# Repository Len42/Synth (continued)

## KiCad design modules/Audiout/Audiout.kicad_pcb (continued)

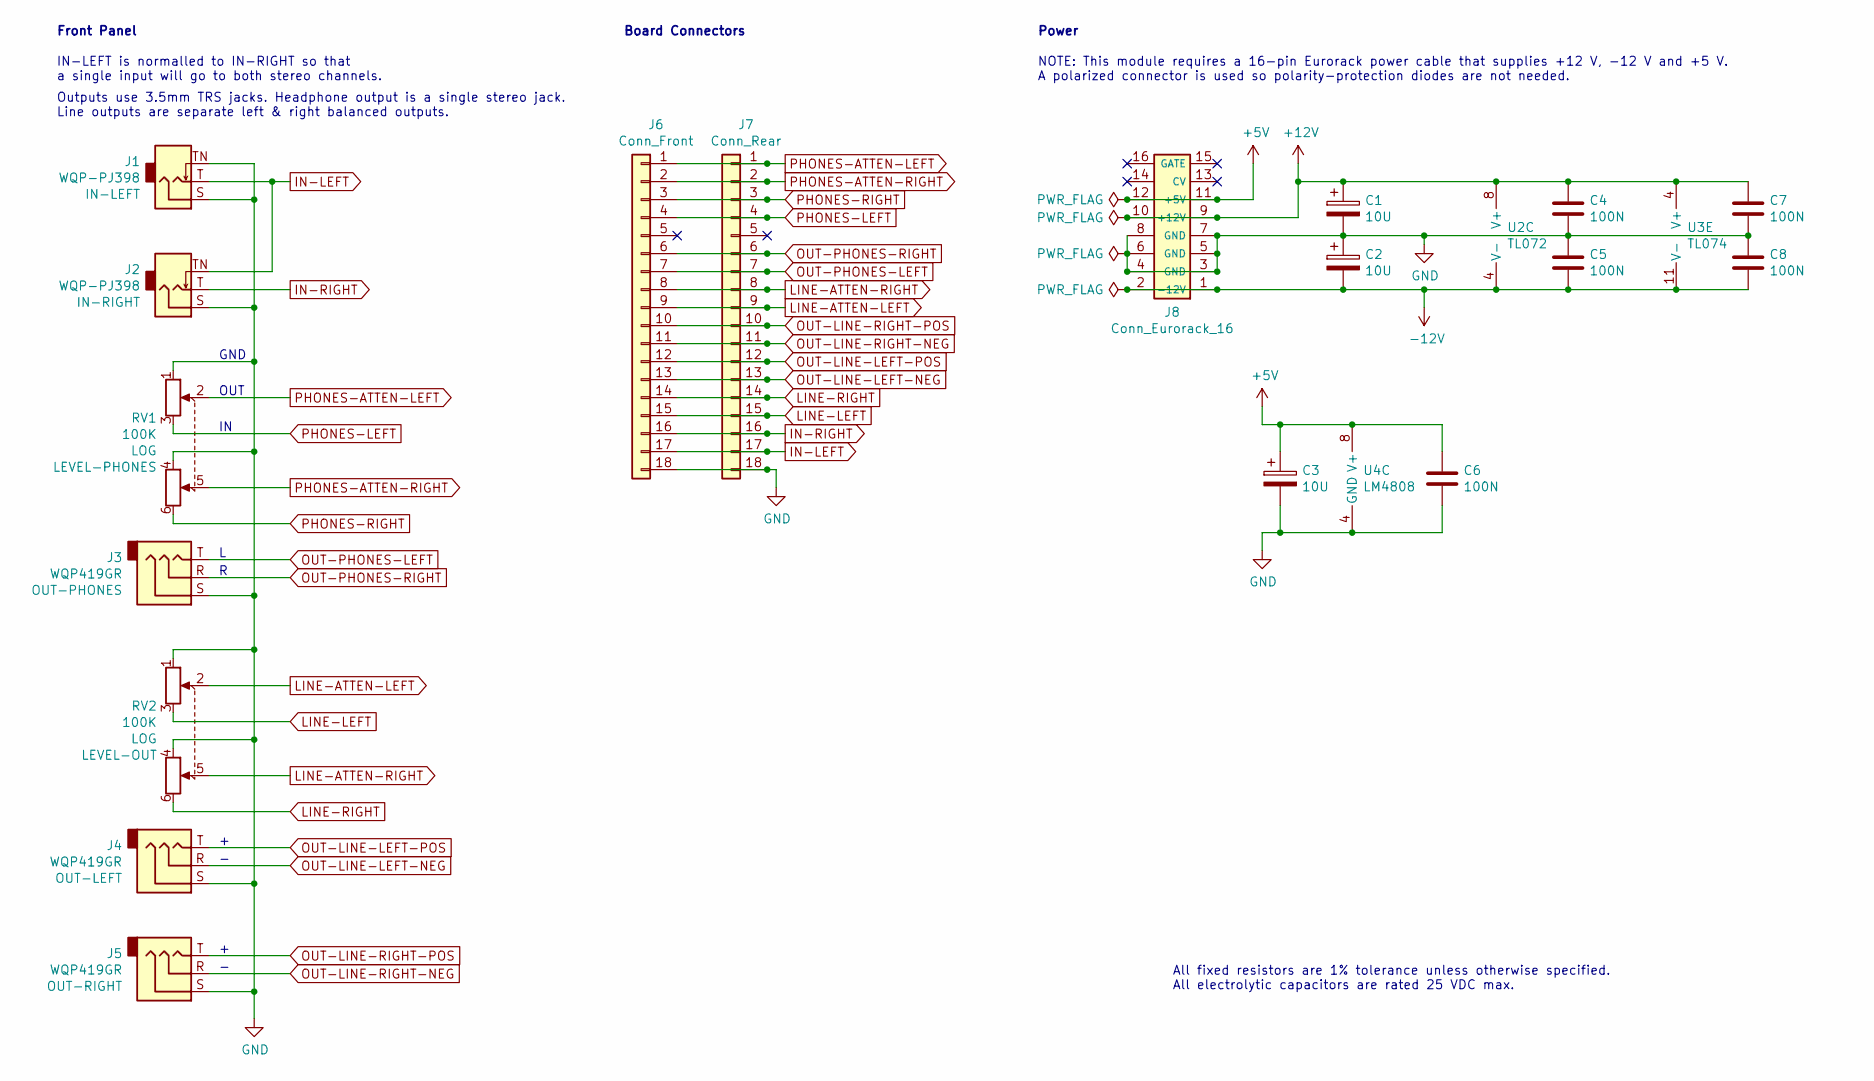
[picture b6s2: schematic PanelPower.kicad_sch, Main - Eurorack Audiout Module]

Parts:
C1, C2: 10U; CP_Radial_D4.0mm_P1.50mm; ManufacturerPartNum EEA-FC1E100
C3: 10U; CP_Radial_D4.0mm_P2.50mm; ManufacturerPartNum EEA-FC1E100
C4, C5, C6, C7, C8: 100N; C_Disc_D5.0mm_W2.5mm_P2.50mm; ManufacturerPartNum FG18X7R1H104KNT06
J1, J2: WQP-PJ398; Jack_3.5mm_QingPu_WQP-PJ398SM_Vertical; ManufacturerPartNum PJ398SM / WQP518MA
J3, J4, J5: WQP419GR; Jack_3.5mm_QingPu_WQP-PJ366ST_Vertical; ManufacturerPartNum PJ366ST / WQP419GR
J6: Conn_Front; PinSocket_1x18_P2.54mm_Vertical
J7: Conn_Rear; PinHeader_1x18_P2.54mm_Horizontal
J8: Conn_Eurorack_16; IDC-Header-Eurorack-16-TH; ManufacturerPartNum 61201621621
RV1, RV2: 100K; Potentiometer_Alpha_RD902F-40-00D_Dual_Vertical; ManufacturerPartNum RD902F-*
U2: TL072; DIP-8_W7.62mm
U3: TL074; DIP-14_W7.62mm
U4: LM4808; Breakout_DIP-SOIC-8_W7.62mm

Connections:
+5V: C3.1, C6.1, J8.11 (+5V), J8.12, U4.8 (V+); also elsewhere on the board
+12V: C1.1, C4.1, C7.1, J8.9 (+12V), J8.10, U2.8 (V+), U3.4 (V+)
-12V: C2.2, C5.2, C8.2, J8.1 (-12V), J8.2, U2.4 (V-), U3.11 (V-)
GND: C1.2, C2.1, C3.2, C4.2, C5.1, C6.2, C7.2, C8.1, J1.S, J1.TN, J2.S, J3.S, J4.S, J5.S, J6.18, J7.18, J8.3 (GND), J8.4, J8.5 (GND), J8.6, J8.7 (GND), J8.8, RV1.1, RV1.4, RV2.1, RV2.4, U4.4 (GND); also elsewhere on the board
IN-LEFT: J1.T, J2.TN, J6.17, J7.17; also elsewhere on the board
IN-RIGHT: J2.T, J6.16, J7.16; also elsewhere on the board
LINE-ATTEN-LEFT: J6.9, J7.9, RV2.2; also elsewhere on the board
LINE-ATTEN-RIGHT: J6.8, J7.8, RV2.5; also elsewhere on the board
LINE-LEFT: J6.15, J7.15, RV2.3; also elsewhere on the board
LINE-RIGHT: J6.14, J7.14, RV2.6; also elsewhere on the board
OUT-LINE-LEFT-NEG: J4.R, J6.13, J7.13; also elsewhere on the board
OUT-LINE-LEFT-POS: J4.T, J6.12, J7.12; also elsewhere on the board
OUT-LINE-RIGHT-NEG: J5.R, J6.11, J7.11; also elsewhere on the board
OUT-LINE-RIGHT-POS: J5.T, J6.10, J7.10; also elsewhere on the board
OUT-PHONES-LEFT: J3.T, J6.7, J7.7; also elsewhere on the board
OUT-PHONES-RIGHT: J3.R, J6.6, J7.6; also elsewhere on the board
PHONES-ATTEN-LEFT: J6.1, J7.1, RV1.2; also elsewhere on the board
PHONES-ATTEN-RIGHT: J6.2, J7.2, RV1.5; also elsewhere on the board
PHONES-LEFT: J6.4, J7.4, RV1.3; also elsewhere on the board
PHONES-RIGHT: J6.3, J7.3, RV1.6; also elsewhere on the board

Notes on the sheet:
IN-LEFT is normalled to IN-RIGHT so that a single input will go to both stereo channels.
All fixed resistors are 1% tolerance unless otherwise specified. All electrolytic capacitors are rated 25 VDC max.
Front Panel
OUT
Board Connectors
GND
NOTE: This module requires a 16-pin Eurorack power cable that supplies +12 V, -12 V and +5 V. A polarized connector is used so polarity-protection diodes are not needed.
Outputs use 3.5mm TRS jacks. Headphone output is a single stereo jack. Line outputs are separate left & right balanced outputs.
Power

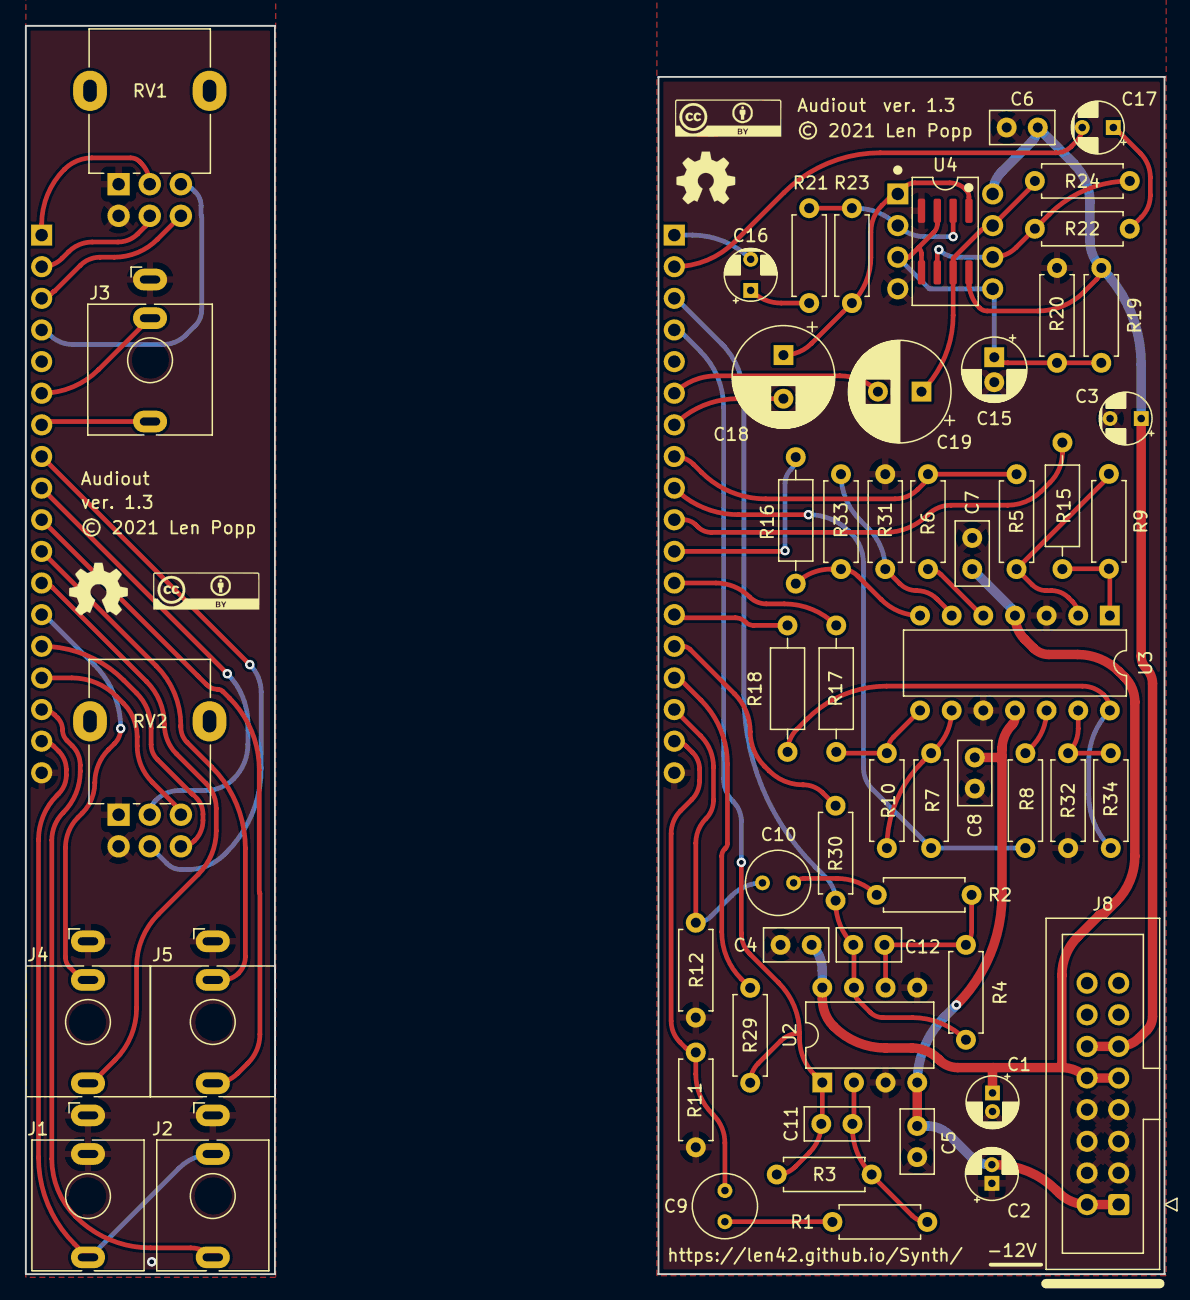
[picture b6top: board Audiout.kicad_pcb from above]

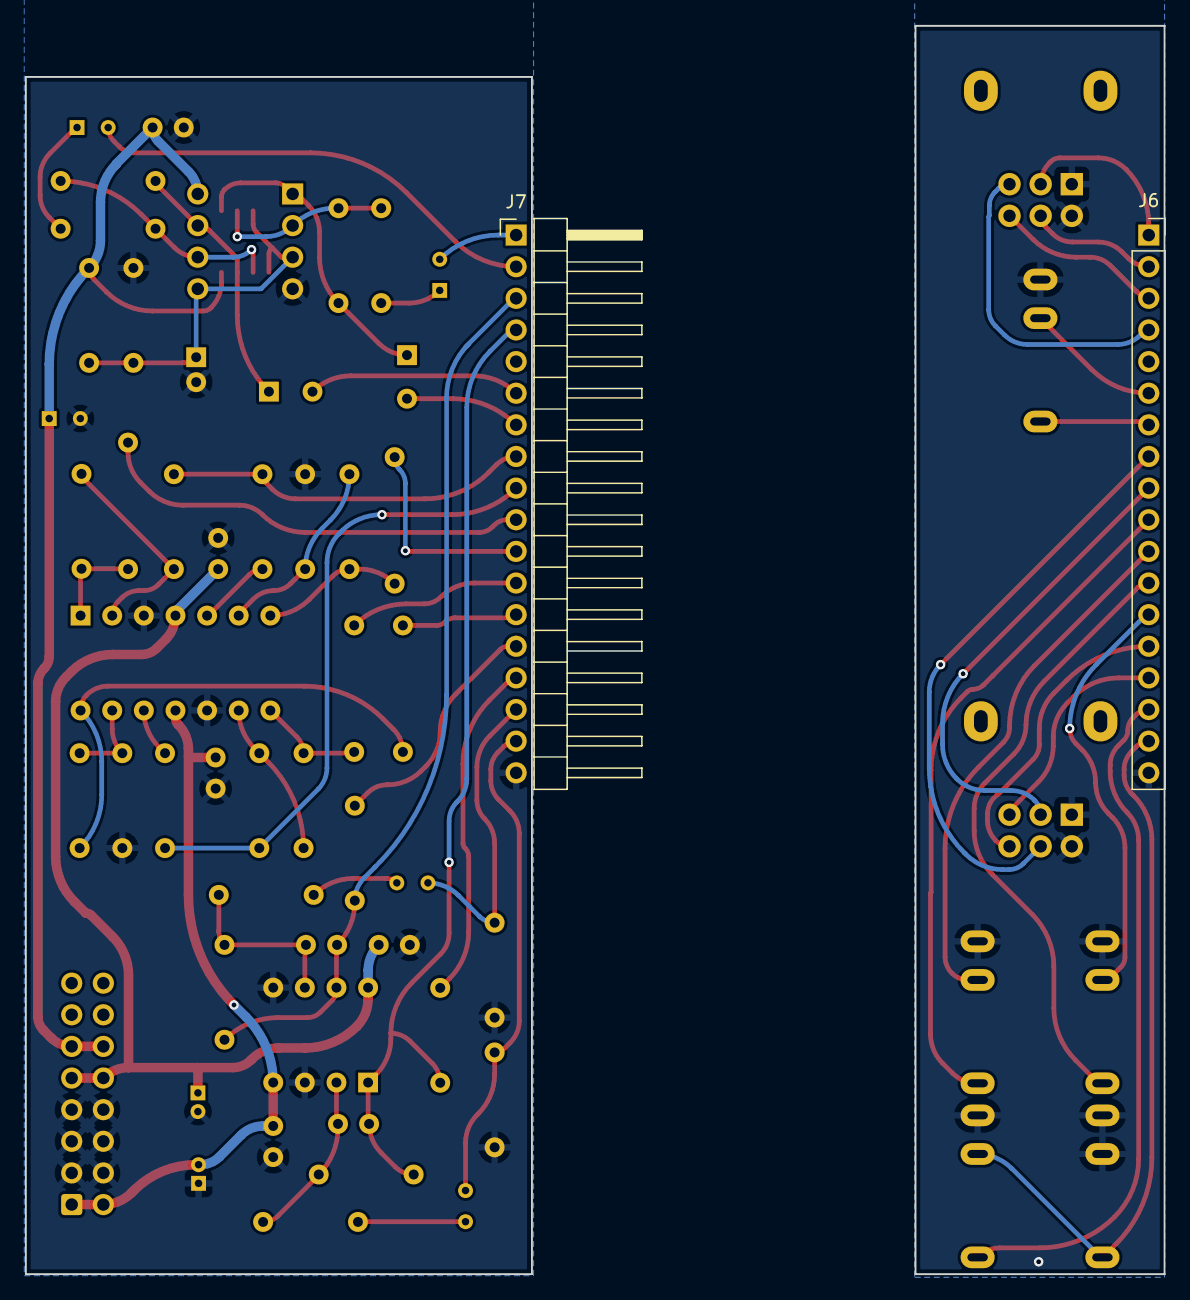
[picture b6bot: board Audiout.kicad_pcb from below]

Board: 2 copper layers, 40.6 x 96.1 mm, 62 parts (2 on the bottom side), 41 nets.

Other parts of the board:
G1, G3: Logo_OSHW
G2, G4: Logo_CC_BY

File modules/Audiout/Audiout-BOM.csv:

Ref,Qty,Value,Value2,Note,Description,Datasheet,Manufacturer,ManuPartNum,Distributor1,DistributorPartNum1,DistributorPartLink1,Distributor2,DistributorPartNum2,DistributorPartLink2,Distributor3,DistributorPartNum3,DistributorPartLink3
"C1 C2 C3","3","10U","25 VDC","","Capacitor - Electrolytic - 12 V decoupling","https://industrial.panasonic.com/cdbs/www-data/pdf/RDF0000/A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","Panasonic","EEA-FC1E100","Mouser","667-EEA-FC1E100","https://www.mouser.ca/ProductDetail/Panasonic/EEA-FC1E100?qs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","","","","","",""
"C4 C5 C6 C7 C8","5","100N","","IC decoupling","Capacitor - Ceramic - IC decoupling","https://product.tdk.com/system/files/dam/doc/product/capacit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","TDK","FG18X7R1H104KNT06","Mouser","810-FG18X7R1H104KNT6","https://www.mouser.ca/ProductDetail/810-FG18X7R1H104KNT6","","","","","",""
"C9 C10","2","10U","NPE","","Capacitor - Non-polarized Electrolytic","https://www.mouser.ca/datasheet/2/315/ABA0000C1053-947510.pdf","Panasonic","ECE-A1EN100UI","Mouser","667-ECE-A1EN100UI","https://www.mouser.ca/ProductDetail/Panasonic/ECE-A1EN100UI?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","","","","","",""
"C11 C12","2","47P","","","Capacitor - Ceramic","https://www.mouser.ca/datasheet/2/427/VISH_S_A0012659393_1-2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","Vishay","K470K15C0GH53L2","Mouser","594-K470K15C0GH53L2","https://www.mouser.ca/ProductDetail/Vishay-BC-Components/K47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","","","","","",""
"C15","1","1U","","","Capacitor - Electrolytic","https://www.mouser.ca/datasheet/2/977/e_YXJ-1601195.pdf","Rubycon","50YXJ1M5X11","Mouser","232-50YXJ1M5X11","https://www.mouser.ca/ProductDetail/Rubycon/50YXJ1M5X11?qs=T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","","","","","",""
"C16 C17","2","4U7","","","Capacitor - Electrolytic","https://www.mouser.ca/datasheet/2/315/ABA0000C1050-947578.pdf","Panasonic","ECE-A1EKA4R7I","Mouser"," 667-ECE-A1EKA4R7I","https://www.mouser.ca/ProductDetail/?qs=rMMd5vBiahozL%2Fri%2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","","","","","",""
"C18 C19","2","220U","","","Capacitor - Electrolytic","https://www.mouser.ca/datasheet/2/315/ABA0000C1024-947657.pdf","Panasonic","EEU-EB1E221SJ","Mouser","667-EEU-EB1E221SJ","https://www.mouser.ca/ProductDetail/Panasonic/EEU-EB1E221SJ?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","","","","","",""
"J1 J2","2","WQP-PJ398","","","Audio Jack, 2 Poles (Mono / TS), Switched T Pole (Normalling), QingPu / Thonkiconn","http://www.qingpu-electronics.com/en/products/WQP-PJ398SM-362.html","QingPu / Thonk","PJ398SM / WQP518MA","Thonk","PJ398SM","https://www.thonk.co.uk/shop/thonkiconn/","SynthCube","WQP518MA","https://synthcube.com/cart/3-5mm-euro-jacks","Adafruit","4031","https://www.adafruit.com/product/4031"
"J3 J4 J5","3","WQP419GR","","","Audio Jack, 3 Poles (Stereo / TRS), QingPu / Thonkiconn","http://www.qingpu-electronics.com/en/products/WQP-PJ366ST-364.html","QingPu / Thonk","PJ366ST / WQP419GR","Thonk","PJ366ST","https://www.thonk.co.uk/shop/thonkiconn/","","","","","",""
"J6","1","Conn_Front","","","Generic connector, single row, 01x18, script generated (kicad-library-utils/schlib/autogen/connector/)","","","","","","","","","","","",""
"J7","1","Conn_Rear","","","Generic connector, single row, 01x18, script generated (kicad-library-utils/schlib/autogen/connector/)","","","","","","","","","","","",""
"J8","1","Conn_Eurorack_16","","","Eurorack 16-pin board power/CV/gate bus connector","https://www.mouser.ca/datasheet/2/445/61201621621-1717735.pdf","Wurth Elektronik","61201621621","Mouser","710-61201621621","https://www.mouser.ca/ProductDetail/Wurth-Elektronik/6120162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","","","","","",""
"R1 R2","2","150K","","","Resistor","https://www.mouser.ca/datasheet/2/447/Yageo_LR_MFR_1-1714151.pdf","YAGEO","MFR-12FTF52-150K","Mouser","603-MFR-12FTF52-150K","https://www.mouser.ca/ProductDetail/YAGEO/MFR-12FTF52-150K?q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","","","","","",""
"R3 R4","2","47K","","","Resistor","https://www.mouser.ca/datasheet/2/447/Yageo_LR_MFR_1-1714151.pdf","YAGEO","MFR-12FTF52-47K","Mouser","603-MFR-12FTF52-47K","https://www.mouser.ca/ProductDetail/YAGEO/MFR-12FTF52-47K?qs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","","","","","",""
"R5 R6 R7 R8 R29 R30 R31 R32","8","10K","","","Resistor","https://www.mouser.ca/datasheet/2/447/Yageo_LR_MFR_1-1714151.pdf","YAGEO","MFR-12FRF52-10K","Mouser","603-MFR-12FRF5210K","https://www.mouser.ca/ProductDetail/YAGEO/MFR-12FRF52-10K?qs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","","","","","",""
"R9 R10","2","43K2","","","Resistor","https://www.mouser.ca/datasheet/2/427/cmfmil-1762972.pdf","Vishay / Dale","RN55D4322FRE6","Mouser","71-RN55D-F-43.2K/R","https://www.mouser.ca/ProductDetail/Vishay-Dale/RN55D4322FRE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","","","","","",""
"R11 R12 R19 R20","4","100K","","","Resistor","https://www.mouser.ca/datasheet/2/447/Yageo_LR_MFR_1-1714151.pdf","YAGEO","MFR-12FTF52-100K","Mouser","603-MFR-12FTF52-100K","https://www.mouser.ca/ProductDetail/603-MFR-12FTF52-100K","","","","","",""
"R15 R16 R17 R18","4","100R","5%, 1/4 W","Output limiting","Resistor","https://www.mouser.ca/datasheet/2/447/Yageo_LR_MFR_1-1714151.pdf","YAGEO","MFR-25FTF52-100R","Mouser","603-MFR-25FTF52-100R","https://www.mouser.ca/ProductDetail/603-MFR-25FTF52-100R","","","","","",""
"R21 R22 R23 R24","4","3K9","","","Resistor","https://www.mouser.ca/datasheet/2/447/Yageo_LR_MFR_1-1714151.pdf","YAGEO","MFR-12FTF52-3K9","Mouser","603-MFR-12FTF52-3K9","https://www.mouser.ca/ProductDetail/603-MFR-12FTF52-3K9","","","","","",""
"R33 R34","2","33K2","","","Resistor","https://www.mouser.ca/datasheet/2/427/cmfmil-1762972.pdf","Vishay / Dale","RN55D3322FRE6","Mouser","71-RN55D-F-33.2K/R","https://www.mouser.ca/ProductDetail/Vishay-Dale/RN55D3322FRE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","","","","","",""
"RV1 RV2","2","100K","LOG","","Dual potentiometer","https://www.thonk.co.uk/wp-content/uploads/Documents/alpha/9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","Alpha","RD902F-*","Thonk","Group_Pot_Alpha_6.35mm","https://www.thonk.co.uk/shop/alpha-9mm-pots/","","","","","",""
"U2","1","TL072","","","Dual Low-Noise JFET-Input Operational Amplifiers, DIP-8/SOIC-8","http://www.ti.com/lit/ds/symlink/tl071.pdf","Texas Instruments","TL072BCP","Mouser","595-TL072BCP","https://www.mouser.ca/ProductDetail/Texas-Instruments/TL072B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","","","","","",""
"U3","1","TL074","","","Quad Low-Noise JFET-Input Operational Amplifiers, DIP-14/SOIC-14","http://www.ti.com/lit/ds/symlink/tl071.pdf","Texas Instruments","TL074BCN","Mouser","595-TL074BCN","https://www.mouser.ca/ProductDetail/?qs=vxEfx8VrU7BHurOY5iQd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","","","","","",""
"U4","1","LM4808","","","Dual Audio Amplifiers","https://www.ti.com/lit/ds/symlink/lm4808.pdf","Texas Instruments","LM4808MX/NOPB","Mouser","595-LM4808MX/NOPB","https://www.mouser.ca/ProductDetail/?qs=2k4gZbgf%2F9mzy9kYxp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","","","","","",""
